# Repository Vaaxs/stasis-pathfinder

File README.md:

Hello, this is my first Project for Stasis.

I followed the tutorial for the Pathfinder while adding a knob/rotary encoder and using that for most of my uniqueness.

More images and progress can be found in my journals.

My Pathfinder has a button that puts power to the LED, and a knob that gives a value in the Serial monitor that can also reset back to zero. 

Image of Bill of Materials

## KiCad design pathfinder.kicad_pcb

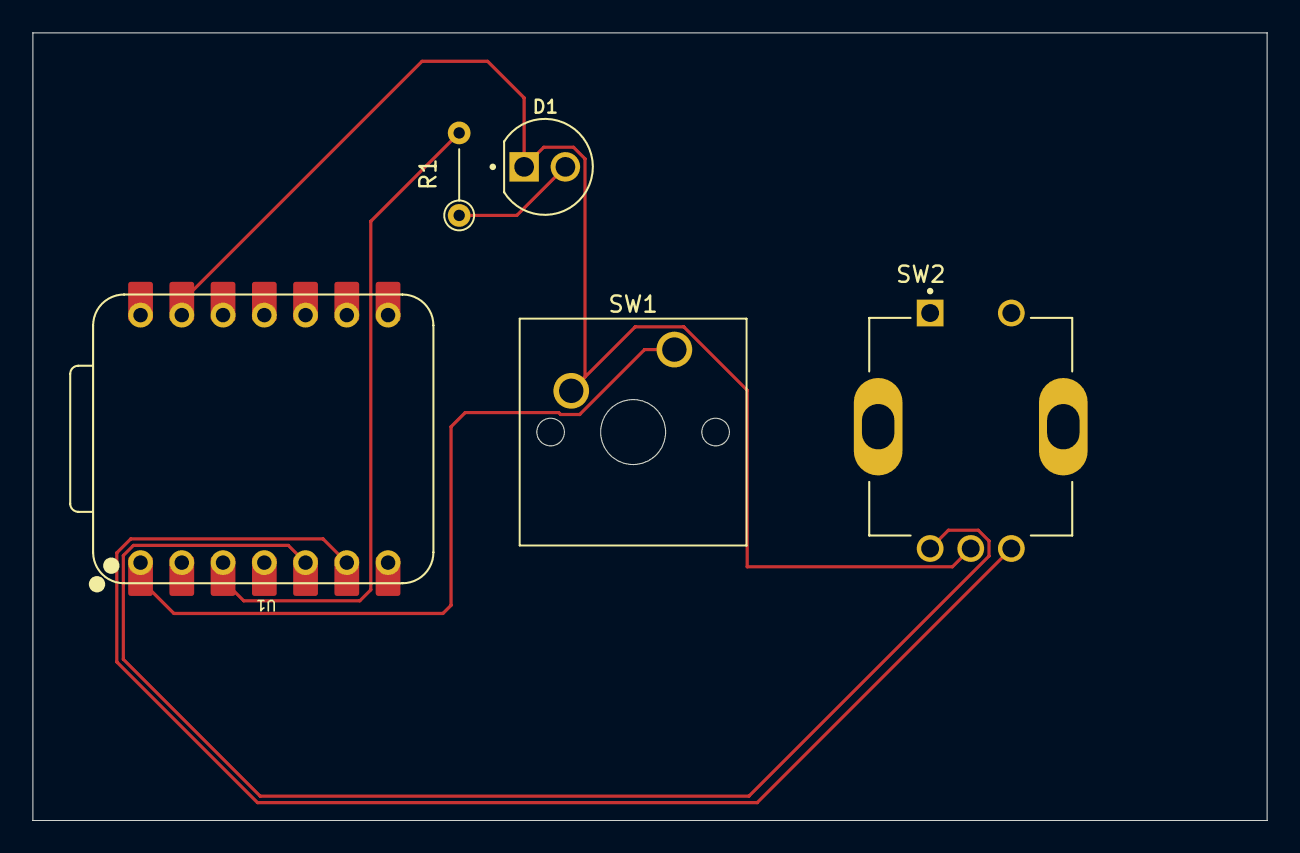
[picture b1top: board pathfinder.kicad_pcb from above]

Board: 2 copper layers, 76.0 x 48.5 mm, 5 parts (0 on the bottom side), 6 nets.

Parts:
D1: L08R5000Q1; LEDRD254W57D500H1070
R1: R; R_Axial_DIN0204_L3.6mm_D1.6mm_P5.08mm_Vertical
SW1: SW_Push; SW_Cherry_MX_1.00u_PCB
SW2: RotaryEncoder_Switch; XDCR_PEC11R-4220F-S0012
U1: XIAO-RP2040-DIP

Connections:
/LED1: R1.2, U1.3 (P28_A2_D2)
/button1: SW1.1, U1.1 (P26_A0_D0)
GND: D1.C, SW1.2, SW2.C, U1.13 (GND)
unnamed: D1.A, R1.1
unnamed: SW2.A, U1.5 (P6_SDA_D4)
unnamed: SW2.B, U1.6 (P7_SCL_D5)

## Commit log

2026-04-03 Schematic, PCB, and Arduino Code!!
2026-04-03 Added 3D Step, Bill of Materials, and Production files
